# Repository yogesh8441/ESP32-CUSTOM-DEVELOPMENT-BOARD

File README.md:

# ESP32-CUSTOM-DEVELOPMENT-BOARD

A custom-designed **ESP32-WROOM-32D Development Board** developed using **KiCad 10**. This project demonstrates the complete PCB design workflow, including schematic design, PCB layout, routing, ground plane implementation, ERC/DRC verification, and generation of manufacturing-ready Gerber files.

---

## 📖 Project Overview

This development board is designed for embedded systems and IoT applications. The board integrates the ESP32-WROOM-32D module with USB programming, power regulation, communication interfaces, and peripheral connectors while following standard PCB design practices.

---

## ✨ Features

- ESP32-WROOM-32D Microcontroller
- CH340C USB-to-UART Interface
- AP2112K-3.3 Voltage Regulator
- USB Programming Support
- UART Communication
- GPIO Expansion Headers
- 16×2 LCD Interface
- 7-Segment Display Interface
- VSPI Interface
- Crystal Oscillator Circuit
- Decoupling Capacitors
- 2-Layer PCB Design
- Ground Plane Implementation
- ERC & DRC Verified
- Manufacturing Ready Gerber Files

---

# 📷 Project Images

## Schematic

---

## PCB Top View

---

## PCB Bottom View

---

## ⚙️ Hardware Specifications

| Parameter | Specification |
|-----------|---------------|
| Microcontroller | ESP32-WROOM-32D |
| USB Interface | CH340C |
| Voltage Regulator | AP2112K-3.3 |
| PCB Layers | 2 |
| PCB Thickness | 1.6 mm |
| Copper Thickness | 1 oz |
| PCB Software | KiCad 10 |
| Manufacturing | JLCPCB Compatible |

---

## 📁 Repository Structure

```text
ESP32-CUSTOM-DEVELOPMENT-BOARD/
│
├── Image/
│   ├── PCB_Top.png
│   ├── PCB_Bottom.png
│   └── Schematic.png
│
├── Schematic/
│   └── ESP32_Project.kicad_sch
│
├── PCB/
│   └── ESP32_Project.kicad_pcb
│
├── Gerber/
│   └── ESP32_Gerber.zip
│
├── Documents/
│
├── README.md
└── LICENSE
```

---

## 🔄 PCB Design Workflow

1. Requirement Analysis
2. Circuit Design
3. Schematic Capture
4. Footprint Assignment
5. PCB Component Placement
6. PCB Routing
7. Ground Plane Implementation
8. ERC Verification
9. DRC Verification
10. Gerber File Generation
11. PCB Manufacturing

---

## 🏭 Manufacturing

The generated Gerber files are manufacturing-ready and can be directly uploaded to PCB fabrication services such as:

- JLCPCB
- PCBWay
- NextPCB

---

## 🚀 Future Improvements

- USB Type-C Interface
- ESD Protection
- Reverse Polarity Protection
- Test Points
- Buck Converter Based Power Supply
- Improved EMI/EMC Performance

---

## 👨‍💻 Author

**Yogesh Kumar**

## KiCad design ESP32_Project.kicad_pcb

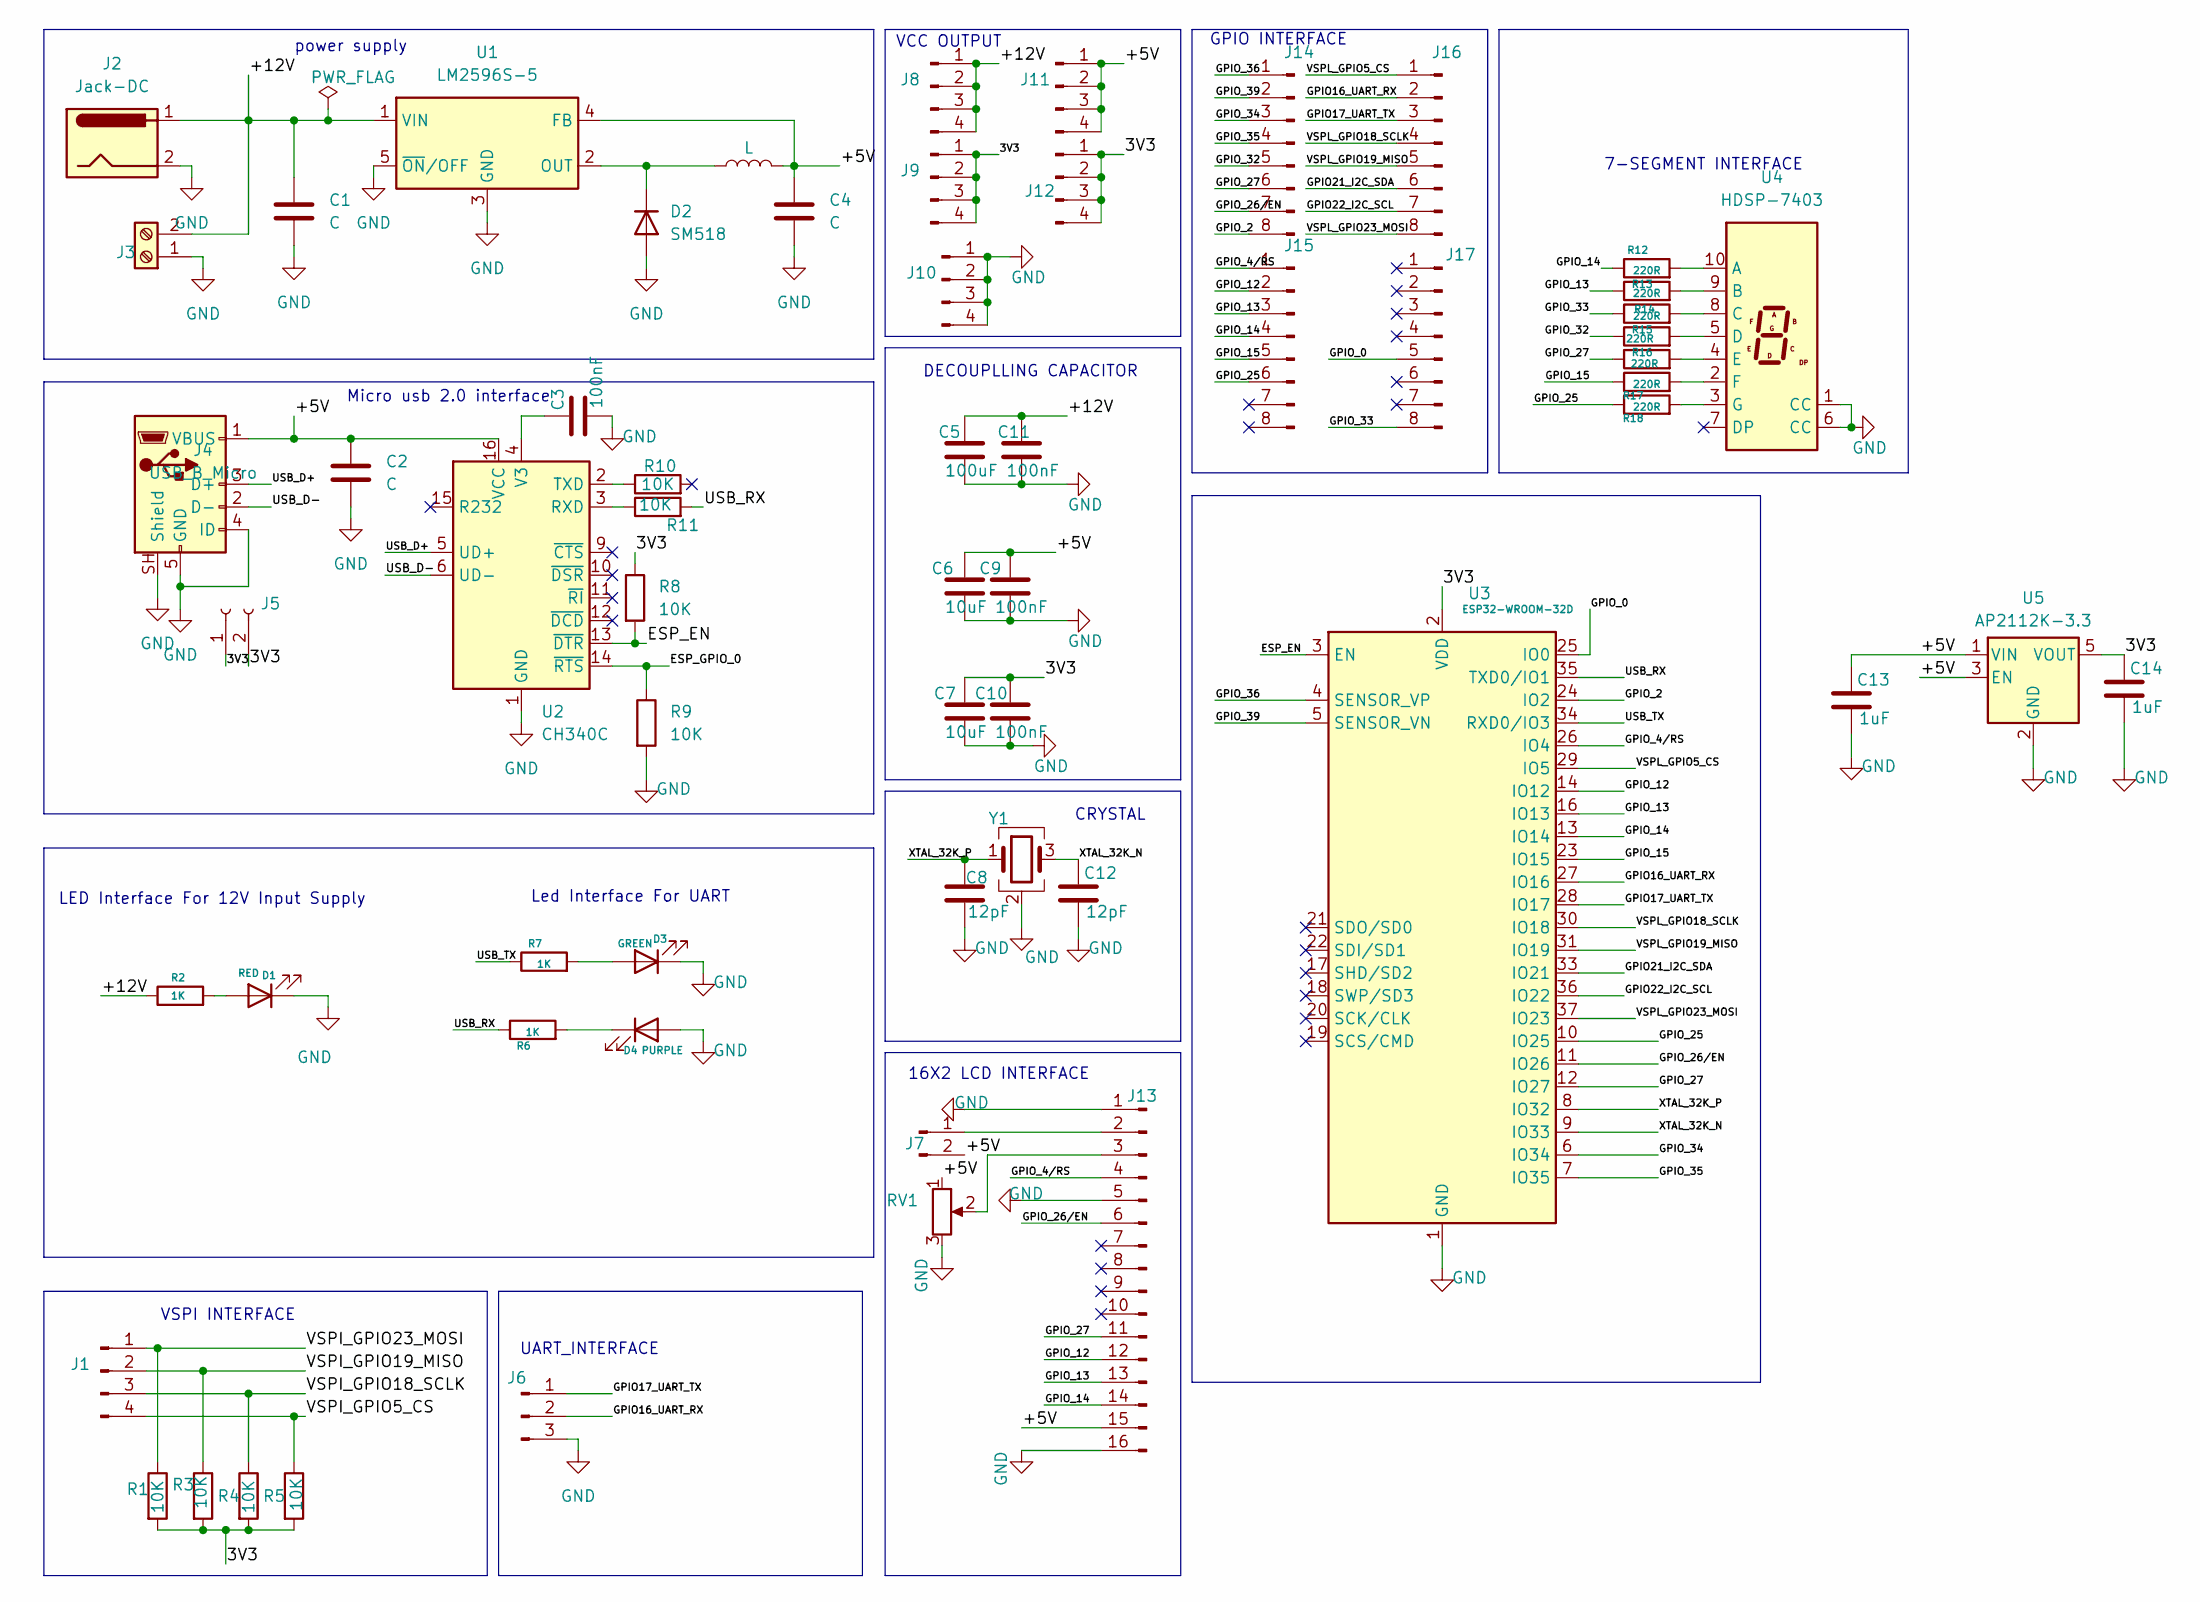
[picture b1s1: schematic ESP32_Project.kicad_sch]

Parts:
C1, C2, C4: C; C_0805_2012Metric_Pad1.18x1.45mm_HandSolder
C3, C9, C10, C11: 100nF; C_0805_2012Metric_Pad1.18x1.45mm_HandSolder
C5: 100uF; C_0805_2012Metric_Pad1.18x1.45mm_HandSolder
C6, C7: 10uF; C_0805_2012Metric_Pad1.18x1.45mm_HandSolder
C8, C12: 12pF; C_0805_2012Metric_Pad1.18x1.45mm_HandSolder
C13, C14: 1uF; C_0805_2012Metric_Pad1.18x1.45mm_HandSolder
D1: RED; LED_0805_2012Metric
D2: SM518; D_DO-41_SOD81_P10.16mm_Horizontal
D3: GREEN; LED_0805_2012Metric
D4: PURPLE; LED_0805_2012Metric
J1, J8, J9, J10, J11, J12: Conn_01x04_Pin; FanPinHeader_1x04_P2.54mm_Vertical
J2: Jack-DC; BarrelJack_SwitchcraftConxall_RAPC10U_Horizontal
J3: Screw_Terminal_01x02; TerminalBlock_Phoenix_MKDS-1,5-2-5.08_1x02_P5.08mm_Horizont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
J4: USB_B_Micro; USB_Micro-AB_Molex_47590-0001
J5: Conn_01x02_Socket; Molex_SL_171971-0002_1x02_P2.54mm_Vertical
J6: Conn_01x03_Pin; FanPinHeader_1x03_P2.54mm_Vertical
J7: Conn_01x02_Pin; PinHeader_1x02_P2.54mm_Vertical
J13: Conn_01x16_Pin; PinHeader_1x16_P2.54mm_Vertical
J14, J15, J16, J17: Conn_01x08_Pin; Molex_KK-254_AE-6410-08A_1x08_P2.54mm_Vertical
L1: L; L_0805_2012Metric_Pad1.05x1.20mm_HandSolder
R1, R3, R4, R5, R8, R9, R10, R11: 10K; R_0805_2012Metric
R2, R6, R7: 1K; R_0805_2012Metric
R12, R13, R14, R15, R16, R17, R18: 220R; R_0805_2012Metric
RV1: R_Potentiometer; Potentiometer_Vishay_148-149_Single_Horizontal
U1: LM2596S-5; TO-263-5_TabPin3
U2: CH340C; SOIC-16_3.9x9.9mm_P1.27mm
U3: ESP32-WROOM-32D
U4: HDSP-7403; HDSP-7401
U5: AP2112K-3.3; SOT-23-5
Y1: Crystal_GND24; Crystal_SMD_0603-4Pin_6.0x3.5mm

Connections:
/3V3: C7.1, C10.1, C14.1, J5.1, J5.2, J9.1, J9.2, J9.3, J9.4, J12.1, J12.2, J12.3, J12.4, R1.2, R3.2, R4.2, R5.2, R8.1, U3.2 (VDD), U5.5 (VOUT)
/+5V: C2.1, C4.1, C6.1, C9.1, C13.1, J4.1 (VBUS), J7.2, J11.1, J11.2, J11.3, J11.4, J13.15, L1.2, RV1.1, U1.4 (FB), U2.16 (VCC), U5.1 (VIN), U5.3 (EN)
/+12V: C1.1, C5.1, C11.1, J2.1, J3.2, J8.1, J8.2, J8.3, J8.4, R2.1, U1.1 (VIN)
/ESP_EN: R8.2, U2.13 (~DTR), U3.3 (EN)
/ESP_GPIO_0: R9.1, U2.14 (~RTS)
/GPIO16_UART_RX: J6.2, J16.2, U3.27 (IO16)
/GPIO17_UART_TX: J6.1, J16.3, U3.28 (IO17)
/GPIO21_I2C_SDA: J16.6, U3.33 (IO21)
/GPIO22_I2C_SCL: J16.7, U3.36 (IO22)
/GPIO_0: J17.5, U3.25 (IO0)
/GPIO_2: J14.8, U3.24 (IO2)
/GPIO_4/RS: J13.4, J15.1, U3.26 (IO4)
/GPIO_12: J13.12, J15.2, U3.14 (IO12)
/GPIO_13: J13.13, J15.3, R13.1, U3.16 (IO13)
/GPIO_14: J13.14, J15.4, R12.1, U3.13 (IO14)
/GPIO_15: J15.5, R17.1, U3.23 (IO15)
/GPIO_25: J15.6, R18.1, U3.10 (IO25)
/GPIO_26/EN: J13.6, J14.7, U3.11 (IO26)
/GPIO_27: J13.11, J14.6, R16.1, U3.12 (IO27)
/GPIO_32: J14.5, R15.1
/GPIO_33: J17.8, R14.1
/GPIO_34: J14.3, U3.6 (IO34)
/GPIO_35: J14.4, U3.7 (IO35)
/GPIO_36: J14.1, U3.4 (SENSOR_VP)
/GPIO_39: J14.2, U3.5 (SENSOR_VN)
/USB_D+: J4.3 (D+), U2.5 (UD+)
/USB_D-: J4.2 (D-), U2.6 (UD-)
/USB_RX: R6.1, R11.2, U3.35 (TXD0/IO1)
/USB_TX: R7.1, U3.34 (RXD0/IO3)
/VSPI_GPIO5_CS: J1.4, R5.1
/VSPI_GPIO18_SCLK: J1.3, R4.1
/VSPI_GPIO19_MISO: J1.2, R3.1
/VSPI_GPIO23_MOSI: J1.1, R1.1
/VSPL_GPIO5_CS: J16.1, U3.29 (IO5)
/VSPL_GPIO18_SCLK: J16.4, U3.30 (IO18)
/VSPL_GPIO19_MISO: J16.5, U3.31 (IO19)
/VSPL_GPIO23_MOSI: J16.8, U3.37 (IO23)
/XTAL_32K_N: C12.1, U3.9 (IO33), Y1.3
/XTAL_32K_P: C8.1, U3.8 (IO32), Y1.1
GND: C1.2, C2.2, C3.2, C4.2, C5.2, C6.2, C7.2, C8.2, C9.2, C10.2, C11.2, C12.2, C13.2, C14.2, D1.1 (K), D2.2 (A), D3.1 (K), D4.2 (A), J2.2, J3.1, J4.4 (ID), J4.5 (GND), J4.SH (Shield), J6.3, J10.1, J10.2, J10.3, J10.4, J13.1, J13.5, J13.16, R9.2, RV1.3, U1.3 (GND), U1.5 (~ON/OFF), U2.1 (GND), U3.1 (GND), U3.15 (GND), U3.38 (GND), U3.39 (GND), U4.1 (CC), U4.6 (CC), U5.2 (GND), Y1.2 (G), Y1.4 (G)
unnamed: D1.2 (A), R2.2
unnamed: D2.1 (K), L1.1, U1.2 (OUT)
unnamed: D3.2 (A), R7.2
unnamed: D4.1 (K), R6.2
unnamed: J7.1, J13.2
unnamed: J13.3, RV1.2
unnamed: R11.1, U2.3 (RXD)
unnamed: R10.1, U2.2 (TXD)
unnamed: C3.1, U2.4 (V3)
unnamed: R12.2, U4.10 (A)
unnamed: R13.2, U4.9 (B)
unnamed: R14.2, U4.8 (C)
unnamed: R15.2, U4.5 (D)
unnamed: R16.2, U4.4 (E)
unnamed: R17.2, U4.2 (F)
unnamed: R18.2, U4.3 (G)

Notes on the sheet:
CRYSTAL
GPIO INTERFACE
power supply
VSPI INTERFACE
7-SEGMENT INTERFACE
Micro usb 2.0 interface
DECOUPLLING CAPACITOR
16X2 LCD INTERFACE
VCC OUTPUT
LED Interface For 12V Input Supply
UART_INTERFACE
Led Interface For UART

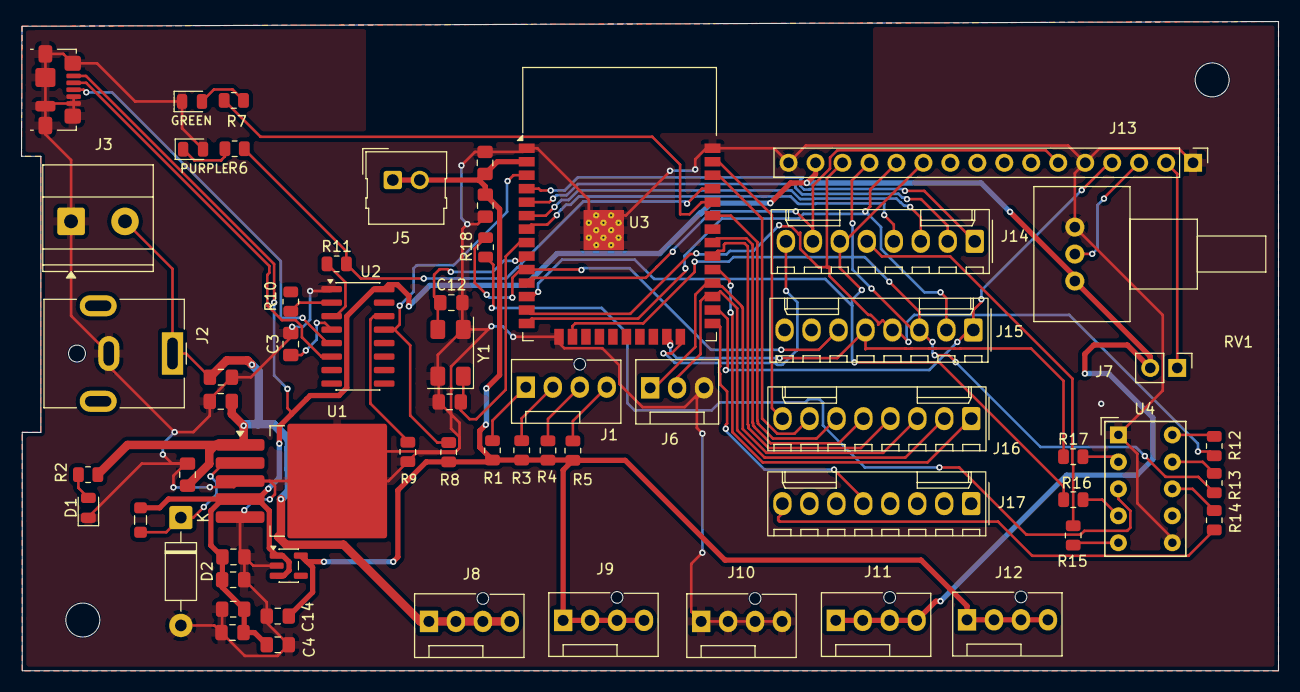
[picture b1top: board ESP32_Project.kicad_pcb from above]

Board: 2 copper layers, 118.4 x 61.2 mm, 61 parts (0 on the bottom side), 56 nets.

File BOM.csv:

"Id";"Designator";"Footprint";"Quantity";"Designation";"Supplier and ref";
1;"C1, C2, C4";"C_0805_2012Metric_Pad1.18x1.45mm_HandSolder";3;"C";;;
2;"C3, C9, C10, C11";"C_0805_2012Metric_Pad1.18x1.45mm_HandSolder";4;"100nF";;;
3;"C5";"C_0805_2012Metric_Pad1.18x1.45mm_HandSolder";1;"100uF";;;
4;"C6, C7";"C_0805_2012Metric_Pad1.18x1.45mm_HandSolder";2;"10uF";;;
5;"C8, C12";"C_0805_2012Metric_Pad1.18x1.45mm_HandSolder";2;"12pF";;;
6;"C13, C14";"C_0805_2012Metric_Pad1.18x1.45mm_HandSolder";2;"1uF";;;
7;"D1";"LED_0805_2012Metric";1;"RED";;;
8;"D2";"D_DO-41_SOD81_P10.16mm_Horizontal";1;"SM518";;;
9;"D3";"LED_0805_2012Metric";1;"GREEN";;;
10;"D4";"LED_0805_2012Metric";1;"PURPLE";;;
11;"J1, J8, J9, J10, J11, J12";"FanPinHeader_1x04_P2.54mm_Vertical";6;"Conn_01x04_Pin";;;
12;"J2";"BarrelJack_CUI_PJ-063AH_Horizontal";1;"Jack-DC";;;
13;"J3";"TerminalBlock_Phoenix_MKDS-1,5-2-5.08_1x02_P5.08mm_Horizontal";1;"Screw_Terminal_01x02";;;
14;"J4";"USB_Micro-B_Molex_47346-0001";1;"USB_B_Micro";;;
15;"J5";"Molex_SL_171971-0002_1x02_P2.54mm_Vertical";1;"Conn_01x02_Socket";;;
16;"J6";"FanPinHeader_1x03_P2.54mm_Vertical";1;"Conn_01x03_Pin";;;
17;"J7";"PinHeader_1x02_P2.54mm_Vertical";1;"Conn_01x02_Pin";;;
18;"J13";"PinHeader_1x16_P2.54mm_Vertical";1;"Conn_01x16_Pin";;;
19;"J14, J15, J16, J17";"Molex_KK-254_AE-6410-08A_1x08_P2.54mm_Vertical";4;"Conn_01x08_Pin";;;
20;"L1";"L_0805_2012Metric_Pad1.05x1.20mm_HandSolder";1;"L";;;
21;"R1, R3, R4, R5, R8, R9, R10, R11";"R_0805_2012Metric";8;"10K";;;
22;"R2, R6, R7";"R_0805_2012Metric";3;"1K";;;
23;"R12, R13, R14, R15, R16, R17, R18";"R_0805_2012Metric";7;"220R";;;
24;"RV1";"Potentiometer_Vishay_148-149_Single_Horizontal";1;"10k";;;
25;"U1";"TO-263-5_TabPin3";1;"LM2596S-5";;;
26;"U2";"SOIC-16_3.9x9.9mm_P1.27mm";1;"CH340C";;;
27;"U3";"ESP32-WROOM-32D";1;"ESP32-WROOM-32D";;;
28;"U4";"HDSP-7401";1;"HDSP-7403";;;
29;"U5";"SOT-23-5";1;"AP2112K-3.3";;;
30;"Y1";"Crystal_SMD_0603-4Pin_6.0x3.5mm";1;"Crystal_GND24";;;
